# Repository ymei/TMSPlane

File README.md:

# Topmetal-S sensor tiled plane

## PCB

We use KiCad and python script to generate schematic, footprint, and PCB layout with minimal manual intervention.

### Procedure:
#### Schematic
1. Draw a Topmetal-S schematic symbol and save in a SCH library ```TMSch.lib```.  ```TMSch.lib``` is symlink-ed to every project.  When modifying the library, open the original ```.lib''' file directly instead of opening the symlinks.
2. run ```GenSch.py``` to generate desired schematic for the TMS array with correct net connectivity.  Here we save the generated file as ```array.sch```, which is a 2nd-level hierarchical schematic under ```Phi10cmBonding.sch```.
3. Open ```Phi10cmBonding.sch``` and generate a netlist.
#### PCB
1. Run ```KiPcbFp.py``` to generate a footprint ```TMS1mm.kicad_mod``` and save it under ```TMPcb.pretty``` which is a footprint library.  One may need to modify ```~/.config/kicad/fp-lib-table``` in order for KiCad to find the library: ```(lib (name Topmetal)(type KiCad)(uri ${KIPRJMOD}/TMPcb.pretty)(options "")(descr "Topmetal bonding footprints"))```.  An alternative is to save a local ```fp-lib-table``` file in the project directory.
2. Use pcbnew manually to setup a PCB `template' with appropriate layer structure, via and track classes etc.  Here we call the template ```template.kicad_pcb```.
3. Draw trace connections within a single footprint using a copy of the template PCB.  Save the single chip SCH and PCB as ```TMS1mm1chip.{sch,kicad_pcb}```.  It is preferable to place TMS1mm module's center at the very center in the unit cell.  It will be used as a reference (local origin).
4. Make a copy of the template PCB and load the netlist into it.  This step will bring all footprints into the PCB.
5. Run ```GenPcb.py``` which references the netlist-loaded PCB and ```TMS1mm1chip.pcb```, and generates the correctly laid out array.
6. **Remember to press `b' in pcbnew** to (re-)fill zones.

## Software
### KiCad

Pull source from https://github.com/KiCad/kicad-source-mirror and compile.

### KiCadScript in Hardware/PCB/KiCadScript/

#### Run scripts in Pcbnew's python shell:
```
import os, sys, runpy
scriptPath = os.environ['KIPRJMOD'] + "/../KiCadScript"
sys.path.append(scriptPath)
sys.argv = ['', '-h']
fileGlobals = runpy.run_path(scriptPath + "/GenSch2ExDAC.py", run_name="__main__")
```

#### Compile C source code to be used in python
```sh
cd KiAuto/hexlib/
python setup.py build
cd build
ln -s lib.freebsd-11.0-STABLE-amd64-2.7/hexlib.so .
```

### KiCad schematic sheets and netnames
KiCad schematic sheets are organized hierarchically.  Sheet paths are named as ```/58F9164E/58F91649``` with the numbers being timestamps in hex format.  Netnames local to a sheet start with a leading ```/```.  Global netnames do not have leading ```/```.

# PCB design and manufacturing

## Manufacturer capabilities

[Sunstone capabilities](http://www.sunstone.com/pcb-manufacturing-capabilities/detailed-capabilities)

|                     | Sunstone preferred | Sunstone capable |
| ------------------- |:------------------ |:---------------- |
| minimum drill size  | 0.008"             | 0.005"           |
| minimum trace width | 0.004" 1 oz Cu     | 0.003"           |
| trace clearance     | 0.004" 1 oz Cu     | 0.003"           |
| through-hole pad dia | 0.018" larger than finished hole dia | 0.016" larger |

Finished hole dia = drill dia - 4mil

### Typical board thickness in inch
```
0.062, 0.093, 0.125, 0.0886(14-layer), 0.0756 (16-layer)
```
1oz copper thickness is 34um (1.34mil)

### Typical drill sizes diameter in inch
```
0.008, 0.014, 0.020, 0.025, 0.029, 0.033, 0.035, 0.040, 0.043, 0.046, 0.052, 0.061,
0.067, 0.079, 0.088, 0.093, 0.100, 0.110, 0.125, 0.141, 0.150, 0.167, 0.192, 0.251
```
For boards thicker than 100mil, usually drill size cannot be smaller than board thickness / 10 (aspect ratio).

### Via
A recommendation: make the drill size diameter the same as the width of the trace, and the pad size roughly twice the diameter.

### Impedance
width/clearance 6mil/6mil and 4mil/4mil on surface layers, 4mil/7mil and 4mil/10mil inner layers are commonly used for Zo=50Ohm, Zdiff=100Ohm.

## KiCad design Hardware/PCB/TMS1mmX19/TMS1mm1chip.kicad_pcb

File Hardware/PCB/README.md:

# TMS1mmX19 Carrier board (with TE0741 FPGA module)

1. Schematic done in KiCad, .asc netlist generated then imported into Mentor PADS for layout.  Remember to delete all **Nets** and modified/unwanted components in PADS before importing .asc.

## Features
1. TMS array power is logic (firmware/software) controlled via LDO EN pins.  Due to power-rail sharing, the relevant bias voltages and serial IO are also controlled by the switches.
2. All LDO design, no DC/DC.  For maximal efficiency, supply 4V power.  Maximum 5V allowed.
3. Serial IO, SDI, SDO, SCK, are multiplexed to drive one column (chain) at a time.  SDI and SCK have `high' as their idle states.

## Power requirement

### LTC2325-16 ADC
1. DVDD2V5 for OVdd: 31.5mA max
2. AVDD3V3 for Vdd : 44.5mA max

5 ADCs total, DVDD2V5: 157.5mA, AVDD3V3: 222.5mA

### LMK00105 for distributing CNVn to ADCs
1. DVDD2V5: 48mA

### 100MHz clock + CDCLVD1208 Clock distribution to ADCs
1. DVDD2V5: 25 + 75mA = 100mA

### 25MHz clock + CDCLVD1208 Clock distribution to SDMs
1. DVDD2V5: 90 + 75mA = 165mA

### ADR3412 + OPA350 for LVDS_VREF
1. DVDD2V5: 1 + 8.5mA = 10mA

DVDD2V5 requires total 545.5mA

# TMS1mmX19 19-chip array bonding board
## Signals and layers
### 16-layer stack-up, for 19-chip array TMS1mmX19.  Thickness 75.6mil, 1oz copper
1  F.Cu    Top copper layer
2  In1.Cu  AGND
3  In2.Cu  GND_NMOSI, DAC_BufferX2_VREF
4  In3.Cu  Gring, Ref3
5  In4.Cu  Ref2
6  In5.Cu  SDM_VDD_Shield, GND_VREF
7  In6.Cu  LVDS_VREF, Ref1
8  In7.Cu  AVDD
9  In8.Cu  AGND fill + RESET (as traces), SDM_testIN (as traces)
10 In9.Cu  DGND fill + slow digital signals: SDI, SDO, SCK
11 In10.Cu SDM_OUT1
12 In11.Cu DGND
13 In12.Cu CLK_P
14 In13.Cu CLK_N, SDM_OUT2
15 In14.Cu DVDD
16 B.Cu    Bottom copper layer

### 3.0mm-thick board produced by Edadoc
```
    Thickness(mil),   material,  DK
F.Cu 0.5oz+plating
    2.73 PP(1080 RC64)           3.81
In1.Cu  1oz
    5.12 CORE                    3.99
In2.Cu  1oz
    6.84 PP(1080 RC64+2116 RC57) 3.91
In3.Cu  1oz
    3.94 CORE                    4.12
In4.Cu  1oz
    5.04 PP(1080 RC64+1080 RC64) 3.81
In5.Cu  1oz
   18.11 CORE                    4.16
In6.Cu  1oz
    3.55 PP(106 RC76+106 RC76)   3.55
In7.Cu  1oz
    5.91 CORE                    4.25
In8.Cu  1oz
    4.01 PP(106 RC76+106 RC76)   3.55
In9.Cu  1oz
   18.11 CORE                    4.16
In10.Cu 1oz
    4.81 PP(1080 RC64+1080 RC64) 3.81
In11.Cu 1oz
    3.94 CORE                    4.12
In12.Cu 1oz
    6.30 PP(2116 RC57+1080 RC64) 3.91
In13.Cu 1oz
    5.12 CORE                    3.99
In14.Cu 1oz
    2.88 PP(1080 RC64)           3.81
B.Cu 0.5oz+plating
```

## FABRICATION NOTES
**All notes are applicable unless otherwise specified**

1. Materials: Green clad FR-4/Epoxy glass or equivalent.  Dielectric constant 4.2+/-0.2.  See cross-section drawing for board thickness, copper weight and layer structures.  RoHS compliant.
2. Components on top (front) and bottom (back) layers.
3. Minimum signal trace width/spacing: 4/4 mils.
4. Drilling.
  1. Minimum drill size is 8mil.
  2. All plated holes are to be plated through and with minimum copper thickness of 1mil.
  3. Drill sizes specified are actual drill sizes.  Finished hole sizes are expected to be 3~4mil smaller than the drill size.
  4. All PTH are to be within +/-3mil from true positions, NPTH to be within +/-2mil.
  5. See hole size table in the supplied NC drill file.
5. Layer-to-layer (pattern-to-pattern) registration (alignment) shall be within +/-5mil.
6. Soldermask: both sides of board, Liquid Photo Imageable, soldermask over bare copper (SMOBC), green.
7. Warpage and twist to meet IPC class II.  Shall not exceed 7mil per inch measured at any location or direction on the board.
8. Silkscreen shall use white non-conductive epoxy or equivalent.  Ink is NOT allowed on exposed plated area.
9. Finish.
  1. Edges to be free of loose silver and rough edge.
  2. Finished board shall not have nicks, scratches, voids, exposed copper, poor plating or mis-drilled holes.
  3. Trace width tolerance = +/-1mil of specified trace width.
  4. ENIG (Electroless nickel immersion gold) finish over copper.
10. Delivered boards shall be free of dirt, oil, finger prints and other contaminants.
11. Remove non-functional pad on all inner layers.
12. Manufacture's UL marking, flammability rating, logo and data code to be placed in silkscreen on bottom side of the board.
13. Impedance control
  1. All 19mil-wide traces on outer layers shall be 50Ohm single-ended +/-10%
  2. All 6mil/6mil width/spacing traces, including 4mil/4mil on outer layers and 4mil/7mil on inner layers shall be 100Ohm differential +/-10%

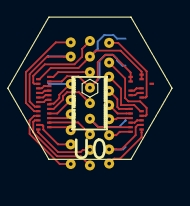
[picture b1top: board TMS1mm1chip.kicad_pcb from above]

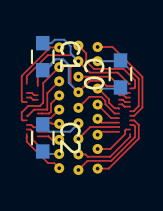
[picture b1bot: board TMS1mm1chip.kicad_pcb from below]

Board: 16 copper layers, 4 parts (3 on the bottom side), 12 nets.

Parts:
C0, C1, C2: 1u; C_0603
U0: TMS1mmAout1or2

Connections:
/AGND: C1.2, C2.2, U0.3, U0.28, U0.47, U0.49
/AVDD: C1.1, C2.1, U0.2, U0.27, U0.48, U0.50
/CSA_VBIASN_{}: U0.41, U0.42
/CSA_VBIASP_{}: U0.43, U0.44
/CSA_VDIS_{}: U0.7, U0.8
/CSA_VREF_{}: U0.5, U0.6
/DGND: C0.2, U0.14
/DVDD: C0.1, U0.13
/SDM_BIAS_{}: U0.29, U0.30
/SDO_{}: U0.24, U0.25
/VCASN_{}: U0.9, U0.10
/VCASP_{}: U0.11, U0.12

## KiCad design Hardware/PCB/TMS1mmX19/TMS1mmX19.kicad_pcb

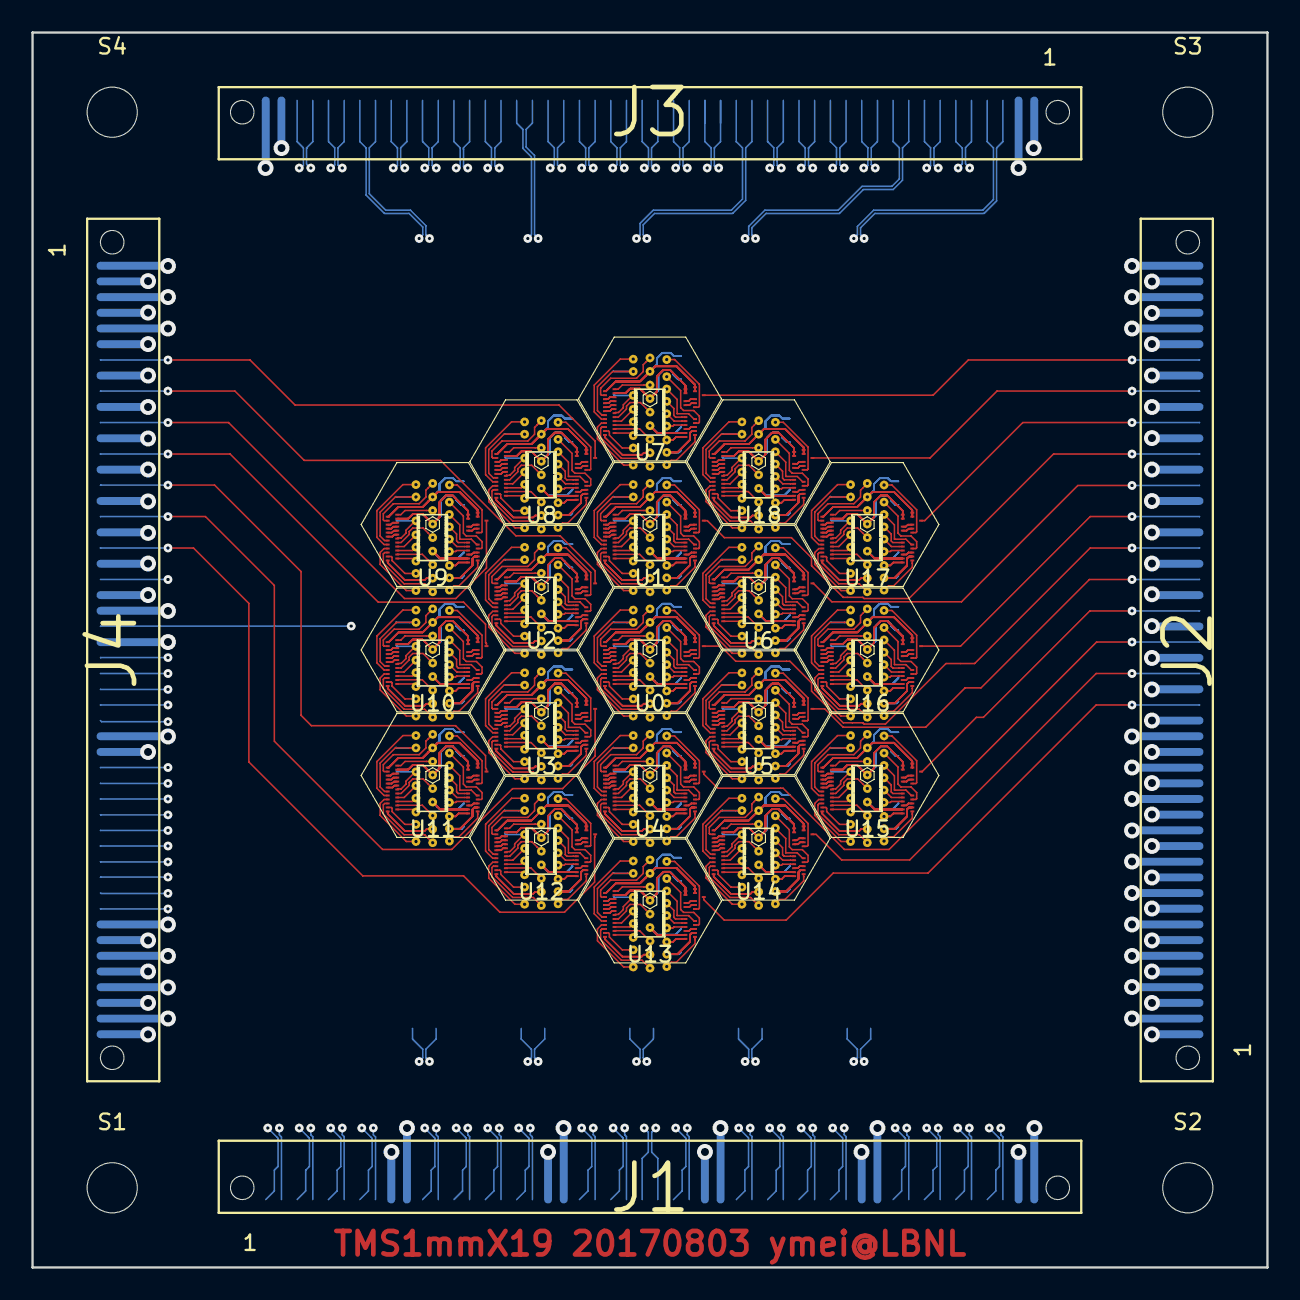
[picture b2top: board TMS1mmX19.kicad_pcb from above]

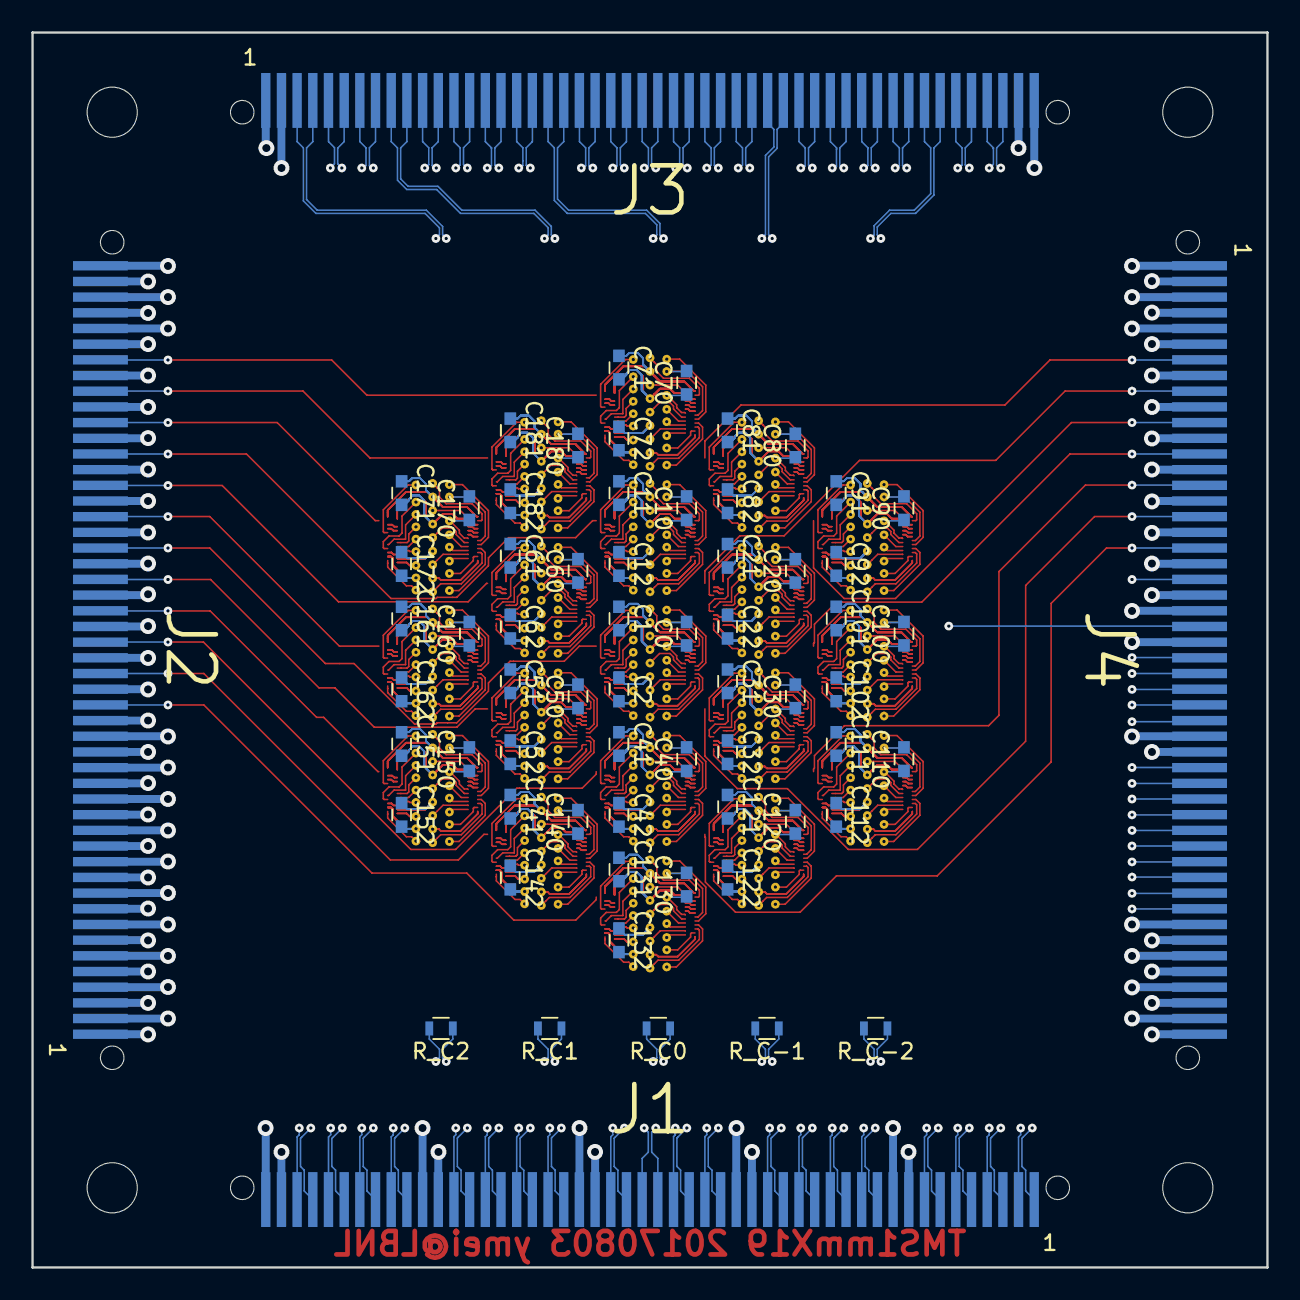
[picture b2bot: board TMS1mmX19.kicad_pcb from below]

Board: 16 copper layers, 78.7 x 78.7 mm, 89 parts (62 on the bottom side), 282 nets.

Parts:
C0, C1, C2, C10, C11, C12, C20, C21, C22, C30, C31, C32, C40, C41, C42, C50, C51, C52, C60, C61, C62, C70, C71, C72, C80, C81, C82, C90, C91, C92, C100, C101, C102, C110, C111, C112, C120, C121, C122, C130, C131, C132, C140, C141, C142, C150, C151, C152, C160, C161, C162, C170, C171, C172, C180, C181, C182: 1u; C_0603
J1, J2, J3, J4: FSI-150-XX-X-S-X-XX; FSI-150-XX-X-S-X-AD-recv-Bot
R_C0, R_C1, R_C2: 100; R_0603
R_C-1, R_C-2: 100; R_0603
S1, S2, S3, S4: Mounting Hole; MountingHole_3.2mm_M3
U0, U1, U2, U3, U4, U5, U6, U7, U8, U9, U10, U11, U12, U13, U14, U15, U16, U17, U18: TMS1mm; TMS1mmAout1or2

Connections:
AGND: C1.2, C2.2, C11.2, C12.2, C21.2, C22.2, C31.2, C32.2, C41.2, C42.2, C51.2, C52.2, C61.2, C62.2, C71.2, C72.2, C81.2, C82.2, C91.2, C92.2, C101.2, C102.2, C111.2, C112.2, C121.2, C122.2, C131.2, C132.2, C141.2, C142.2, C151.2, C152.2, C161.2, C162.2, C171.2, C172.2, C181.2, C182.2, J2.5, J2.6, J2.13, J2.14, J2.15, J2.16, J2.17, J2.18, J2.19, J2.20, J2.21, J2.23, J2.25, J2.27, J2.29, J2.31, J2.33, J2.35, J2.37, J2.39, J2.41, J2.43, J4.5, J4.6, J4.8, J4.10, J4.12, J4.14, J4.16, J4.18, J4.20, J4.22, J4.23, J4.25, U0.3, U0.28, U0.47, U0.49, U1.3, U1.28, U1.47, U1.49, U2.3, U2.28, U2.47, U2.49, U3.3, U3.28, U3.47, U3.49, U4.3, U4.28, U4.47, U4.49, U5.3, U5.28, U5.47, U5.49, U6.3, U6.28, U6.47, U6.49, U7.3, U7.28, U7.47, U7.49, U8.3, U8.28, U8.47, U8.49, U9.3, U9.28, U9.47, U9.49, U10.3, U10.28, U10.47, U10.49, U11.3, U11.28, U11.47, U11.49, U12.3, U12.28, U12.47, U12.49, U13.3, U13.28, U13.47, U13.49, U14.3, U14.28, U14.47, U14.49, U15.3, U15.28, U15.47, U15.49, U16.3, U16.28, U16.47, U16.49, U17.3, U17.28, U17.47, U17.49, U18.3, U18.28, U18.47, U18.49
AOUT1_CSA_0: J2.32, U0.46
AOUT1_CSA_1: J2.38, U1.46
AOUT1_CSA_2: J4.9, U2.46
AOUT1_CSA_3: J4.17, U3.46
AOUT1_CSA_4: J2.26, U4.46
AOUT1_CSA_5: J2.30, U5.46
AOUT1_CSA_6: J2.36, U6.46
AOUT1_CSA_7: J2.44, U7.46
AOUT1_CSA_8: J4.7, U8.46
AOUT1_CSA_9: J4.11, U9.46
AOUT1_CSA_10: J4.13, U10.46
AOUT1_CSA_11: J4.15, U11.46
AOUT1_CSA_12: J4.19, U12.46
AOUT1_CSA_13: J2.22, U13.46
AOUT1_CSA_14: J2.24, U14.46
AOUT1_CSA_15: J2.28, U15.46
AOUT1_CSA_16: J2.34, U16.46
AOUT1_CSA_17: J2.40, U17.46
AOUT1_CSA_18: J2.42, U18.46
AVDD: C1.1, C2.1, C11.1, C12.1, C21.1, C22.1, C31.1, C32.1, C41.1, C42.1, C51.1, C52.1, C61.1, C62.1, C71.1, C72.1, C81.1, C82.1, C91.1, C92.1, C101.1, C102.1, C111.1, C112.1, C121.1, C122.1, C131.1, C132.1, C141.1, C142.1, C151.1, C152.1, C161.1, C162.1, C171.1, C172.1, C181.1, C182.1, J2.9, J2.10, J2.11, J2.12, J2.45, J2.46, J4.43, J4.44, J4.45, J4.46, U0.2, U0.27, U0.48, U0.50, U1.2, U1.27, U1.48, U1.50, U2.2, U2.27, U2.48, U2.50, U3.2, U3.27, U3.48, U3.50, U4.2, U4.27, U4.48, U4.50, U5.2, U5.27, U5.48, U5.50, U6.2, U6.27, U6.48, U6.50, U7.2, U7.27, U7.48, U7.50, U8.2, U8.27, U8.48, U8.50, U9.2, U9.27, U9.48, U9.50, U10.2, U10.27, U10.48, U10.50, U11.2, U11.27, U11.48, U11.50, U12.2, U12.27, U12.48, U12.50, U13.2, U13.27, U13.48, U13.50, U14.2, U14.27, U14.48, U14.50, U15.2, U15.27, U15.48, U15.50, U16.2, U16.27, U16.48, U16.50, U17.2, U17.27, U17.48, U17.50, U18.2, U18.27, U18.48, U18.50
CLK_0_N: J3.20, R_C0.2, U0.21, U1.21, U4.21, U7.21, U13.21
CLK_0_P: J3.19, R_C0.1, U0.22, U1.22, U4.22, U7.22, U13.22
CLK_1_N: J3.10, R_C1.2, U5.21, U6.21, U14.21, U18.21
CLK_1_P: J3.9, R_C1.1, U5.22, U6.22, U14.22, U18.22
CLK_2_N: J3.4, R_C2.2, U15.21, U16.21, U17.21
CLK_2_P: J3.3, R_C2.1, U15.22, U16.22, U17.22
CLK_-1_N: J3.34, R_C-1.2, U2.21, U3.21, U8.21, U12.21
CLK_-1_P: J3.33, R_C-1.1, U2.22, U3.22, U8.22, U12.22
CLK_-2_N: J3.44, R_C-2.2, U9.21, U10.21, U11.21
CLK_-2_P: J3.43, R_C-2.1, U9.22, U10.22, U11.22
CSA_VBIASN_0: U0.41, U0.42
CSA_VBIASN_1: U1.41, U1.42
CSA_VBIASN_2: U2.41, U2.42
CSA_VBIASN_3: U3.41, U3.42
CSA_VBIASN_4: U4.41, U4.42
CSA_VBIASN_5: U5.41, U5.42
CSA_VBIASN_6: U6.41, U6.42
CSA_VBIASN_7: U7.41, U7.42
CSA_VBIASN_8: U8.41, U8.42
CSA_VBIASN_9: U9.41, U9.42
CSA_VBIASN_10: U10.41, U10.42
CSA_VBIASN_11: U11.41, U11.42
CSA_VBIASN_12: U12.41, U12.42
CSA_VBIASN_13: U13.41, U13.42
CSA_VBIASN_14: U14.41, U14.42
CSA_VBIASN_15: U15.41, U15.42
CSA_VBIASN_16: U16.41, U16.42
CSA_VBIASN_17: U17.41, U17.42
CSA_VBIASN_18: U18.41, U18.42
CSA_VBIASP_0: U0.43, U0.44
CSA_VBIASP_1: U1.43, U1.44
CSA_VBIASP_2: U2.43, U2.44
CSA_VBIASP_3: U3.43, U3.44
CSA_VBIASP_4: U4.43, U4.44
CSA_VBIASP_5: U5.43, U5.44
CSA_VBIASP_6: U6.43, U6.44
CSA_VBIASP_7: U7.43, U7.44
CSA_VBIASP_8: U8.43, U8.44
CSA_VBIASP_9: U9.43, U9.44
CSA_VBIASP_10: U10.43, U10.44
CSA_VBIASP_11: U11.43, U11.44
CSA_VBIASP_12: U12.43, U12.44
CSA_VBIASP_13: U13.43, U13.44
CSA_VBIASP_14: U14.43, U14.44
CSA_VBIASP_15: U15.43, U15.44
CSA_VBIASP_16: U16.43, U16.44
CSA_VBIASP_17: U17.43, U17.44
CSA_VBIASP_18: U18.43, U18.44
CSA_VDIS_0: U0.7, U0.8
CSA_VDIS_1: U1.7, U1.8
CSA_VDIS_2: U2.7, U2.8
CSA_VDIS_3: U3.7, U3.8
CSA_VDIS_4: U4.7, U4.8
CSA_VDIS_5: U5.7, U5.8
CSA_VDIS_6: U6.7, U6.8
CSA_VDIS_7: U7.7, U7.8
CSA_VDIS_8: U8.7, U8.8
CSA_VDIS_9: U9.7, U9.8
CSA_VDIS_10: U10.7, U10.8
CSA_VDIS_11: U11.7, U11.8
CSA_VDIS_12: U12.7, U12.8
CSA_VDIS_13: U13.7, U13.8
CSA_VDIS_14: U14.7, U14.8
CSA_VDIS_15: U15.7, U15.8
CSA_VDIS_16: U16.7, U16.8
CSA_VDIS_17: U17.7, U17.8
CSA_VDIS_18: U18.7, U18.8
CSA_VREF_0: U0.5, U0.6
CSA_VREF_1: U1.5, U1.6
CSA_VREF_2: U2.5, U2.6
CSA_VREF_3: U3.5, U3.6
CSA_VREF_4: U4.5, U4.6
CSA_VREF_5: U5.5, U5.6
CSA_VREF_6: U6.5, U6.6
CSA_VREF_7: U7.5, U7.6
CSA_VREF_8: U8.5, U8.6
CSA_VREF_9: U9.5, U9.6
CSA_VREF_10: U10.5, U10.6
CSA_VREF_11: U11.5, U11.6
CSA_VREF_12: U12.5, U12.6
CSA_VREF_13: U13.5, U13.6
CSA_VREF_14: U14.5, U14.6
CSA_VREF_15: U15.5, U15.6
CSA_VREF_16: U16.5, U16.6
CSA_VREF_17: U17.5, U17.6
CSA_VREF_18: U18.5, U18.6
DAC_BufferX2_VREF: J4.47, J4.48, U0.40, U1.40, U2.40, U3.40, U4.40, U5.40, U6.40, U7.40, U8.40, U9.40, U10.40, U11.40, U12.40, U13.40, U14.40, U15.40, U16.40, U17.40, U18.40
DGND: C0.2, C10.2, C20.2, C30.2, C40.2, C50.2, C60.2, C70.2, C80.2, C90.2, C100.2, C110.2, C120.2, C130.2, C140.2, C150.2, C160.2, C170.2, C180.2, J1.9, J1.10, J1.19, J1.20, J1.29, J1.30, J3.49, J3.50, J4.31, J4.32, U0.14, U1.14, U2.14, U3.14, U4.14, U5.14, U6.14, U7.14, U8.14, U9.14, U10.14, U11.14, U12.14, U13.14, U14.14, U15.14, U16.14, U17.14, U18.14
DVDD: C0.1, C10.1, C20.1, C30.1, C40.1, C50.1, C60.1, C70.1, C80.1, C90.1, C100.1, C110.1, C120.1, C130.1, C140.1, C150.1, C160.1, C170.1, C180.1, J1.39, J1.40, J1.49, J1.50, J3.1, J3.2, U0.13, U1.13, U2.13, U3.13, U4.13, U5.13, U6.13, U7.13, U8.13, U9.13, U10.13, U11.13, U12.13, U13.13, U14.13, U15.13, U16.13, U17.13, U18.13
GND_NMOSI: J4.3, J4.4, U0.4, U1.4, U2.4, U3.4, U4.4, U5.4, U6.4, U7.4, U8.4, U9.4, U10.4, U11.4, U12.4, U13.4, U14.4, U15.4, U16.4, U17.4, U18.4
GND_VREF: J2.3, J2.4, U0.31, U1.31, U2.31, U3.31, U4.31, U5.31, U6.31, U7.31, U8.31, U9.31, U10.31, U11.31, U12.31, U13.31, U14.31, U15.31, U16.31, U17.31, U18.31
Gring: J4.1, J4.2, U0.1, U1.1, U2.1, U3.1, U4.1, U5.1, U6.1, U7.1, U8.1, U9.1, U10.1, U11.1, U12.1, U13.1, U14.1, U15.1, U16.1, U17.1, U18.1
LVDS_VREF: J2.49, J2.50, U0.15, U1.15, U2.15, U3.15, U4.15, U5.15, U6.15, U7.15, U8.15, U9.15, U10.15, U11.15, U12.15, U13.15, U14.15, U15.15, U16.15, U17.15, U18.15
RESET: J4.24, U0.16, U1.16, U2.16, U3.16, U4.16, U5.16, U6.16, U7.16, U8.16, U9.16, U10.16, U11.16, U12.16, U13.16, U14.16, U15.16, U16.16, U17.16, U18.16
Ref1: J2.1, J2.2, U0.33, U1.33, U2.33, U3.33, U4.33, U5.33, U6.33, U7.33, U8.33, U9.33, U10.33, U11.33, U12.33, U13.33, U14.33, U15.33, U16.33, U17.33, U18.33
Ref2: J2.7, J2.8, U0.34, U1.34, U2.34, U3.34, U4.34, U5.34, U6.34, U7.34, U8.34, U9.34, U10.34, U11.34, U12.34, U13.34, U14.34, U15.34, U16.34, U17.34, U18.34
Ref3: J4.49, J4.50, U0.32, U1.32, U2.32, U3.32, U4.32, U5.32, U6.32, U7.32, U8.32, U9.32, U10.32, U11.32, U12.32, U13.32, U14.32, U15.32, U16.32, U17.32, U18.32
SCK_0: J4.37, U0.23, U1.23, U4.23, U7.23, U13.23
SCK_1: J4.39, U5.23, U6.23, U14.23, U18.23
SCK_2: J4.41, U15.23, U16.23, U17.23
SCK_-1: J4.35, U2.23, U3.23, U8.23, U12.23
SCK_-2: J4.33, U9.23, U10.23, U11.23
SDM_BIAS_0: U0.29, U0.30
SDM_BIAS_1: U1.29, U1.30
SDM_BIAS_2: U2.29, U2.30
SDM_BIAS_3: U3.29, U3.30
SDM_BIAS_4: U4.29, U4.30
SDM_BIAS_5: U5.29, U5.30
SDM_BIAS_6: U6.29, U6.30
SDM_BIAS_7: U7.29, U7.30
SDM_BIAS_8: U8.29, U8.30
SDM_BIAS_9: U9.29, U9.30
SDM_BIAS_10: U10.29, U10.30
SDM_BIAS_11: U11.29, U11.30
SDM_BIAS_12: U12.29, U12.30
SDM_BIAS_13: U13.29, U13.30
SDM_BIAS_14: U14.29, U14.30
SDM_BIAS_15: U15.29, U15.30
SDM_BIAS_16: U16.29, U16.30
SDM_BIAS_17: U17.29, U17.30
SDM_BIAS_18: U18.29, U18.30
SDM_OUT1_0_N: J3.31, U0.19
SDM_OUT1_0_P: J3.32, U0.20
SDM_OUT1_1_N: J3.27, U1.19
SDM_OUT1_1_P: J3.28, U1.20
SDM_OUT1_2_N: J3.41, U2.19
SDM_OUT1_2_P: J3.42, U2.20
SDM_OUT1_3_N: J1.11, U3.19
SDM_OUT1_3_P: J1.12, U3.20
SDM_OUT1_4_N: J1.21, U4.19
SDM_OUT1_4_P: J1.22, U4.20
SDM_OUT1_5_N: J1.31, U5.19
SDM_OUT1_5_P: J1.32, U5.20
SDM_OUT1_6_N: J3.17, U6.19
SDM_OUT1_6_P: J3.18, U6.20
SDM_OUT1_7_N: J3.23, U7.19
SDM_OUT1_7_P: J3.24, U7.20
SDM_OUT1_8_N: J3.37, U8.19
SDM_OUT1_8_P: J3.38, U8.20
SDM_OUT1_9_N: J3.47, U9.19
SDM_OUT1_9_P: J3.48, U9.20
SDM_OUT1_10_N: J1.1, U10.19
SDM_OUT1_10_P: J1.2, U10.20
SDM_OUT1_11_N: J1.5, U11.19
SDM_OUT1_11_P: J1.6, U11.20
SDM_OUT1_12_N: J1.15, U12.19
SDM_OUT1_12_P: J1.16, U12.20
SDM_OUT1_13_N: J1.25, U13.19
SDM_OUT1_13_P: J1.26, U13.20
SDM_OUT1_14_N: J1.35, U14.19
SDM_OUT1_14_P: J1.36, U14.20
SDM_OUT1_15_N: J1.45, U15.19
SDM_OUT1_15_P: J1.46, U15.20
SDM_OUT1_16_N: J1.41, U16.19
SDM_OUT1_16_P: J1.42, U16.20
SDM_OUT1_17_N: J3.7, U17.19
SDM_OUT1_17_P: J3.8, U17.20
SDM_OUT1_18_N: J3.13, U18.19
SDM_OUT1_18_P: J3.14, U18.20
SDM_OUT2_0_N: J3.30, U0.18
SDM_OUT2_0_P: J3.29, U0.17
SDM_OUT2_1_N: J3.26, U1.18
SDM_OUT2_1_P: J3.25, U1.17
SDM_OUT2_2_N: J3.40, U2.18
SDM_OUT2_2_P: J3.39, U2.17
SDM_OUT2_3_N: J1.14, U3.18
SDM_OUT2_3_P: J1.13, U3.17
SDM_OUT2_4_N: J1.24, U4.18
SDM_OUT2_4_P: J1.23, U4.17
SDM_OUT2_5_N: J1.34, U5.18
SDM_OUT2_5_P: J1.33, U5.17
SDM_OUT2_6_N: J3.16, U6.18
SDM_OUT2_6_P: J3.15, U6.17
SDM_OUT2_7_N: J3.22, U7.18
SDM_OUT2_7_P: J3.21, U7.17
SDM_OUT2_8_N: J3.36, U8.18
SDM_OUT2_8_P: J3.35, U8.17
SDM_OUT2_9_N: J3.46, U9.18
SDM_OUT2_9_P: J3.45, U9.17
SDM_OUT2_10_N: J1.4, U10.18
SDM_OUT2_10_P: J1.3, U10.17
SDM_OUT2_11_N: J1.8, U11.18
SDM_OUT2_11_P: J1.7, U11.17
SDM_OUT2_12_N: J1.18, U12.18
SDM_OUT2_12_P: J1.17, U12.17
SDM_OUT2_13_N: J1.28, U13.18
SDM_OUT2_13_P: J1.27, U13.17
SDM_OUT2_14_N: J1.38, U14.18
SDM_OUT2_14_P: J1.37, U14.17
SDM_OUT2_15_N: J1.48, U15.18
SDM_OUT2_15_P: J1.47, U15.17
SDM_OUT2_16_N: J1.44, U16.18
SDM_OUT2_16_P: J1.43, U16.17
SDM_OUT2_17_N: J3.6, U17.18
SDM_OUT2_17_P: J3.5, U17.17
SDM_OUT2_18_N: J3.12, U18.18
SDM_OUT2_18_P: J3.11, U18.17
SDM_VDD_Shield: J2.47, J2.48, U0.26, U1.26, U2.26, U3.26, U4.26, U5.26, U6.26, U7.26, U8.26, U9.26, U10.26, U11.26, U12.26, U13.26, U14.26, U15.26, U16.26, U17.26, U18.26
SDM_testIN: J4.21, U0.35, U1.35, U2.35, U3.35, U4.35, U5.35, U6.35, U7.35, U8.35, U9.35, U10.35, U11.35, U12.35, U13.35, U14.35, U15.35, U16.35, U17.35, U18.35
SDO_0: U0.25, U1.24
SDO_1: U1.25, U7.24
SDO_2: U2.25, U8.24
SDO_3: U2.24, U3.25
SDO_4: U0.24, U4.25
SDO_5: U5.25, U6.24
SDO_6: U6.25, U18.24
SDO_7: J4.28, U7.25
SDO_8: J4.29, U8.25
SDO_9: J4.30, U9.25
SDO_10: U9.24, U10.25
SDO_11: U10.24, U11.25
SDO_12: U3.24, U12.25
SDO_13: U4.24, U13.25
SDO_14: U5.24, U14.25
SDO_15: U15.25, U16.24
SDO_16: U16.25, U17.24
SDO_17: J4.26, U17.25
SDO_18: J4.27, U18.25
SDO_26: J4.34, U11.24
SDO_27: J4.36, U12.24
SDO_28: J4.38, U13.24
SDO_29: J4.40, U14.24
SDO_30: J4.42, U15.24
VCASN_0: U0.9, U0.10
VCASN_1: U1.9, U1.10
VCASN_2: U2.9, U2.10
VCASN_3: U3.9, U3.10
VCASN_4: U4.9, U4.10
VCASN_5: U5.9, U5.10
VCASN_6: U6.9, U6.10
VCASN_7: U7.9, U7.10
VCASN_8: U8.9, U8.10
VCASN_9: U9.9, U9.10
VCASN_10: U10.9, U10.10
VCASN_11: U11.9, U11.10
VCASN_12: U12.9, U12.10
VCASN_13: U13.9, U13.10
VCASN_14: U14.9, U14.10
VCASN_15: U15.9, U15.10
VCASN_16: U16.9, U16.10
VCASN_17: U17.9, U17.10
VCASN_18: U18.9, U18.10
VCASP_0: U0.11, U0.12
VCASP_1: U1.11, U1.12
VCASP_2: U2.11, U2.12
VCASP_3: U3.11, U3.12
VCASP_4: U4.11, U4.12
VCASP_5: U5.11, U5.12
VCASP_6: U6.11, U6.12
VCASP_7: U7.11, U7.12
VCASP_8: U8.11, U8.12
VCASP_9: U9.11, U9.12
VCASP_10: U10.11, U10.12
VCASP_11: U11.11, U11.12
VCASP_12: U12.11, U12.12
VCASP_13: U13.11, U13.12
VCASP_14: U14.11, U14.12
VCASP_15: U15.11, U15.12
VCASP_16: U16.11, U16.12
VCASP_17: U17.11, U17.12
VCASP_18: U18.11, U18.12

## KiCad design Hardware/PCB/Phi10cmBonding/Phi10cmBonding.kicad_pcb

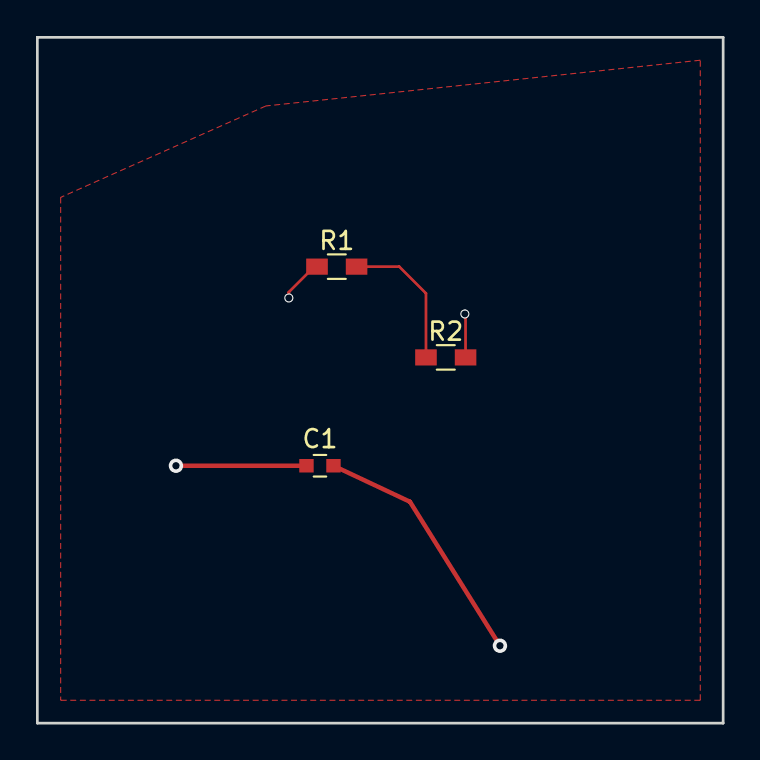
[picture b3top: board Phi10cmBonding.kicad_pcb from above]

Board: 4 copper layers, 38.1 x 38.1 mm, 3 parts (0 on the bottom side), 3 nets.

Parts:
C1: C_0603
R1: 100; R_0603_HandSoldering
R2: 1k; R_0603_HandSoldering

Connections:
/GND: C1.2, R2.2
/R12: R1.2, R2.1
/VDD: C1.1, R1.1

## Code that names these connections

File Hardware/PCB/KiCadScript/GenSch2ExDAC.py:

#!/usr/bin/env python

## \file
# Generate schematic of Topmetal-S array using 2 external DACs per sensor.
#
# usage: GenSch2ExDAC.py [-h] [-n NCHIPS] [-p PITCH] ofn
#
# positional arguments:
#   ofn                   Output file [.sch]
#
# optional arguments:
#   -h, --help            show this help message and exit
#   -n NCHIPS, --nchips NCHIPS
#                         Number of chips to place [127]
#   -p PITCH, --pitch PITCH
#                         Pitch between chip symbols [4000]
#

from __future__ import print_function

import sys
import argparse

from KiAuto import *
from KiAuto.HexLib import *

TMS1mmNetTemplate = {
    1 : "Gring",
    2 : "AVDD",
    3 : "AGND",
    4 : "GND_NMOSI",
    5 : "CSA_VREF_{}", # DAC6
    6 : "CSA_VREF_{}",
    7 : "CSA_VDIS_{}", # DAC5
    8 : "CSA_VDIS_{}",
    9 : "VCASN_{}",    # DAC3
    10 : "VCASN_{}",
    11 : "VCASP_{}",   # DAC4
    12 : "VCASP_{}",
    13 : "DVDD",
    14 : "DGND",
    15 : "LVDS_VREF",
    16 : "RESET",
    17 : "SDM_OUT2_{}_P",
    18 : "SDM_OUT2_{}_N",
    19 : "SDM_OUT1_{}_N",
    20 : "SDM_OUT1_{}_P",
    21 : "CLK_{}_N",
    22 : "CLK_{}_P",
    23 : "SCK_{}",
    24 : "SDO_{}", # this sensor's SDI fed by another chip's SDO
    25 : "SDO_{}",
    26 : "SDM_VDD_Shield",
    27 : "AVDD",
    28 : "AGND",
    29 : "SDM_BIAS_{}", # IN
    30 : "SDM_BIAS_{}", # OUT
    31 : "GND_VREF",
    32 : "Ref3",
    33 : "Ref1",
    34 : "Ref2",
    35 : "SDM_testIN",
    36 : "", # AOUT3N_CSA
    37 : "", # AOUT3P_CSA
    38 : "", # AOUT_BufferX2
    39 : "", # BufferX2_testIN
    40 : "DAC_BufferX2_VREF",
    41 : "CSA_VBIASN_{}",
    42 : "CSA_VBIASN_{}", # DAC1
    43 : "CSA_VBIASP_{}",
    44 : "CSA_VBIASP_{}", # DAC2
    45 : "", # AOUT2_CSA
    46 : "AOUT1_CSA_{}",
    47 : "AGND",
    48 : "AVDD",
    49 : "AGND",
    50 : "AVDD"
}

def get_labels(id, template):
    hex = Hex()
    labels = []
    qr = hex.l2qr(id)
    l = hex.qr2l((qr[0], qr[1]-1))
    for i in xrange(len(template)):
        v = template[i+1]
        if 'SCK_{}' in v or 'CLK_{}' in v:
            labels.append(v.format(qr[0]))
        elif i+1 == 24:
            labels.append(v.format(l))
        elif '{}' in v:
            labels.append(v.format(id))
        else:
            labels.append(v)
    return labels

if __name__ == "__main__":

    parser = argparse.ArgumentParser()
    parser.add_argument("-n", "--nchips", type=int, default=127,
                        help="Number of chips to place [127]")
    parser.add_argument("-p", "--pitch", type=int, default=4000,
                        help="Pitch between chip symbols [4000]")
    parser.add_argument("-l", "--ltype", type=str, default="G", choices=["L", "H", "G"],
                        help="Label type, L (local), H, or G (global) [G]")
    parser.add_argument("ofn", type=str, default="out.sch",
                        help="Output file [.sch]")
    args = parser.parse_args()

    hex = Hex()
    # print(TMS1mmNetTemplate[5].format(5))

    sch = KiSch()
    sheetid = 1
    sheettot = 1
    if args.ltype != "L":
        sheetid = 2
        sheettot = 3
    sch.set_descr(paper="User 20000 22000", sheetid=sheetid, sheettot=sheettot,
                  title="Topmetal-S array")
    sch.add_to_libs("LIBS:TMSch\n")
    comps = ""
    schCenter = (10000, 11000)
    cnYoff = 1650
    cnXp = 500

    for i in xrange(args.nchips):
        qr = hex.l2qr(i)
        xy = hex.qr2xy(args.pitch, qr)

        loc = (int(xy[0])+schCenter[0], schCenter[1]-int(xy[1]))
        labels = get_labels(i, TMS1mmNetTemplate)
        Un = KiSchCompTMS1mm("U{}".format(i), loc, val="TMS1mm", fp="Topmetal:TMS1mm2ExDAC",
                             labels=labels, ltype=args.ltype)
        comps += str(Un)
        Cn = []
        Ln = []
        for j in xrange(3):
            cloc = (loc[0]-cnXp+j*cnXp, loc[1]+cnYoff)
            Cn.append(KiSchCompC("C{}".format(i*10+j), cloc, val="1u", fp="Capacitors_SMD:C_0603"))
            if j == 0:
                Ln.append(KiSchLabel("DGND", (cloc[0], cloc[1]+150), ltype=args.ltype))
                Ln.append(KiSchLabel("DVDD", (cloc[0], cloc[1]-150), ltype=args.ltype))
            else:
                Ln.append(KiSchLabel("AGND", (cloc[0], cloc[1]+150), ltype=args.ltype))
                Ln.append(KiSchLabel("AVDD", (cloc[0], cloc[1]-150), ltype=args.ltype))
        for Ci in Cn:
            comps += str(Ci)
        for Li in Ln:
            comps += str(Li)

    sch.set_content(comps)
    with open(args.ofn, "w") as ofile:
        ofile.write(str(sch))

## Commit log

2017-03-28 Initial KiCad script and example project
2017-04-05 First example of correct net handling and zone filling
2017-04-10 Add Topmetal-S schematic symbol lib and KiSch class to add it.
2017-04-11 Add KiPcbFp footprint generation
2017-04-13 Add HexLib and single TMS1 sch with netname label handling.
2017-04-13 Create a reasonable unit cell.
2017-04-17 Achieve reasonable array generation.
2017-04-21 Add FSI-150-XX-X-D-X-XX connector symbol and footprint
2017-04-25 Add FSI-150-XX-X-D-X-AD-solder-Front and a FPGA carrier board sketch
2017-04-28 Update SNx5LVDx386 and FSI footprint
2017-05-31 First array of 19 using 2 external DACs per sensor.
2017-07-15 First array of 19 with Aout1or2
2017-08-03 First production-ready PCB/TMS1mmX19
2017-08-10 TMS1mmX19Carrier work-in-progress
2017-08-12 TMS1mmX19Carrier first version sent out for PADS layout.
2017-08-13 Update CSA_EXT CON and power CON before sending out for PADS layout.
2017-08-17 Corrected the hole locations, SM1~4, for TE0741.
2017-08-21 First import of KC705 project
2017-08-25 First incorporation of aurora_64b66b Verified correct UFC message send/receive and bit order.
2017-08-27 gig_eth --- aurora UFC loopback.
2017-08-28 First import of TE0741-2C1 XC7K160T-FFG676-2 control_interface is connected to aurora64b66b as well.
2017-10-08 Lower aurora_64b66b line rate to 3.125Gbps Files under src/aurora64b66b/ for the two devices are identical but are kept as separate copies. Reformat .xdc using set_property -dict
2017-10-08 TCP server 2 streams.
    KC705 on tcp port 1024.
    TE0741 on tcp port 1025.
    Stream #1 works only when TCP_USE_FIFO='1'.
2017-10-09 Establish basic function of DA8568C, I2C, TMS serial io.
2017-10-12 LTC2325-16 ADC read and serial-to-parallel conversion.
2017-10-13 Implement TMS SDM receiver.
2017-10-15 Implement data tunnel through aurora to KC705 and read by control_interface fifo.
    Correct adc_cnv timing and time constraints.
    Add ASYNC_REG for clock domain crossing.
    Correct asynchronous clock group interaction.
2017-11-08 Implement the first GUI Tuner for TMS1mmX19 array.
    Add acquire_from_datafifo() to command.py for reading the datafifo via TCP.
    Correct BPI/SPI config flash info in Firmware/README.md.
2017-11-10 Implement sensor working mode selection through argparse.
    Add socket.MSG_WAITALL into recv() calls.
    Reduce wait in tms_sio_rw().
    Add SDM data demux and data saving to files.
2017-11-16 Move demux_fifodata and save_data to C.
    Create sigproc.{h,c,py} and modify setup.py for compilation.
2017-11-20 Add trigger to data_sampler_fifo and SDMdemo plot.
    Had to use a timer (2**27 * 10ns = 1.34s) for auto-trigger if
    external TRIG doesn't arrive. Using the timer and ~busy to reset
    fifo_rdwidth_reducer seem to be the way to avoid data corruption.
    Need deeper investigation to figure out why using trig_synced to
    reset fifo_rdwidth_reducer results in data corruption.
2017-11-28 Add configuration saving into .json file to TMS1mmX19Tuner.py.
    Add visible channel selection for waveform plotting.
    Update SDMdemo.
2018-02-12 Implement single-channel Auto Tuner.
    Include a version of Differential Evolution written in Python.
    Implement pulse measurement in sigproc.c and in Python.
2018-03-25 Add WavX19 plots. Widen AutoTune DE bounds.
